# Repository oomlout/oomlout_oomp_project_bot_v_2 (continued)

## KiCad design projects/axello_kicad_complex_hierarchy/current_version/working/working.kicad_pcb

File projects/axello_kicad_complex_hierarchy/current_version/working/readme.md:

# kicad
 
## summary 
* id: axello_kicad_complex_hierarchy
* user: axello
* name: kicad
* board: complex_hierarchy
* repo: https://github.com/axello/kicad
* src_file_repo_kicad_pcb: demos/complex_hierarchy/complex_hierarchy.kicad_pcb
* src_file_repo_kicad_pcb_link: https://github.com/axello/kicad/tree/master/demos/complex_hierarchy/complex_hierarchy.kicad_pcb
* src_file_repo_kicad_sch: demos/complex_hierarchy/ampli_ht.kicad_sch
* src_file_repo_kicad_sch_link: https://github.com/axello/kicad/tree/master/demos/complex_hierarchy/ampli_ht.kicad_sch

* src_file_repo_sch: Arduino_Mega_433Mhz_Shield/Arduino_Mega.sch
* src_file_repo_sch_link: https://github.com/axello/kicad/tree/master/Arduino_Mega_433Mhz_Shield/Arduino_Mega.sch
* full details link: https://github.com/oomlout/oomlout_oomp_project_bot_v_2/tree/main/projects/axello_kicad_complex_hierarchy/current_version/working  

## pcb  

[board (pdf)](working.pdf)  

## working_bom
| Id | Designator | Footprint | Quantity | Designation | Supplier and ref |  | None | 
| --- | --- | --- | --- | --- | --- | --- | --- | 
| 1 | C2 | CP_Axial_L10.0mm_D4.5mm_P15.00mm_Horizontal | 1 | 47uF/20V |  |  | [''] | 
| 2 | C9 | CP_Axial_L11.0mm_D6.0mm_P18.00mm_Horizontal | 1 | 47uF/63V |  |  | [''] | 
| 3 | C10,C11 | CP_Axial_L10.0mm_D4.5mm_P15.00mm_Horizontal | 2 | 10uF |  |  | [''] | 
| 4 | Q1,Q3,Q5,Q7 | TO-92_HandSolder | 4 | MPSA92 |  |  | [''] | 
| 5 | Q6,Q8,Q2,Q4 | TO-92_HandSolder | 4 | MPSA42 |  |  | [''] | 
| 6 | RV1,RV2 | Potentiometer_Bourns_3266W_Vertical | 2 | 4,7K |  |  | [''] | 
| 7 | U2 | TO-92_HandSolder | 1 | 78L05 |  |  | [''] | 
| 8 | R19,R18,R9,R8,R24,R23 | R_Axial_DIN0204_L3.6mm_D1.6mm_P7.62mm_Horizontal | 6 | 1K |  |  | [''] | 
| 9 | R6,R16,R7,R17 | R_Axial_DIN0204_L3.6mm_D1.6mm_P7.62mm_Horizontal | 4 | 22K |  |  | [''] | 
| 10 | R15,R5,R27,R25 | R_Axial_DIN0204_L3.6mm_D1.6mm_P7.62mm_Horizontal | 4 | 47 |  |  | [''] | 
| 11 | R14,R12,R4,R28,R26,R22 | R_Axial_DIN0204_L3.6mm_D1.6mm_P7.62mm_Horizontal | 6 | 220K |  |  | [''] | 
| 12 | R13,R3 | R_Axial_DIN0204_L3.6mm_D1.6mm_P7.62mm_Horizontal | 2 | 470 |  |  | [''] | 
| 13 | R11,R21 | R_Axial_DIN0204_L3.6mm_D1.6mm_P7.62mm_Horizontal | 2 | 4,7K |  |  | [''] | 
| 14 | R10,R20 | R_Axial_DIN0204_L3.6mm_D1.6mm_P7.62mm_Horizontal | 2 | 5,6K |  |  | [''] | 
| 15 | U4,U3 | DIP-8_W7.62mm_LongPads | 2 | LM358N |  |  | [''] | 
| 16 | U1 | DIP-8_W7.62mm_LongPads | 1 | ICL7660 |  |  | [''] | 
| 17 | C8,C5 | C_Disc_D5.0mm_W2.5mm_P5.00mm | 2 | 820pF |  |  | [''] | 
| 18 | C7,C4 | C_Disc_D5.0mm_W2.5mm_P5.00mm | 2 | 4.7nF |  |  | [''] | 
| 19 | C6,C3 | C_Disc_D5.0mm_W2.5mm_P5.00mm | 2 | 15nF |  |  | [''] | 
| 20 | C12,C14 | C_Disc_D5.0mm_W2.5mm_P5.00mm | 2 | 150nF |  |  | [''] | 
| 21 | D1 | D_DO-41_SOD81_P12.70mm_Horizontal | 1 | 1N4007 |  |  | [''] | 
| 22 | D5,D8,D2,D3,D7,D6,D4,D9 | D_DO-35_SOD27_P7.62mm_Horizontal | 8 | 1N4148 |  |  | [''] | 
| 23 | P1,P2,P4,P3,P6,P5 | Altech_AK300_1x02_P5.00mm_45-Degree | 6 | CONN_2 |  |  | [''] | 
| 24 | C1 | CP_Axial_L10.0mm_D4.5mm_P15.00mm_Horizontal | 1 | 47uF |  |  | [''] |

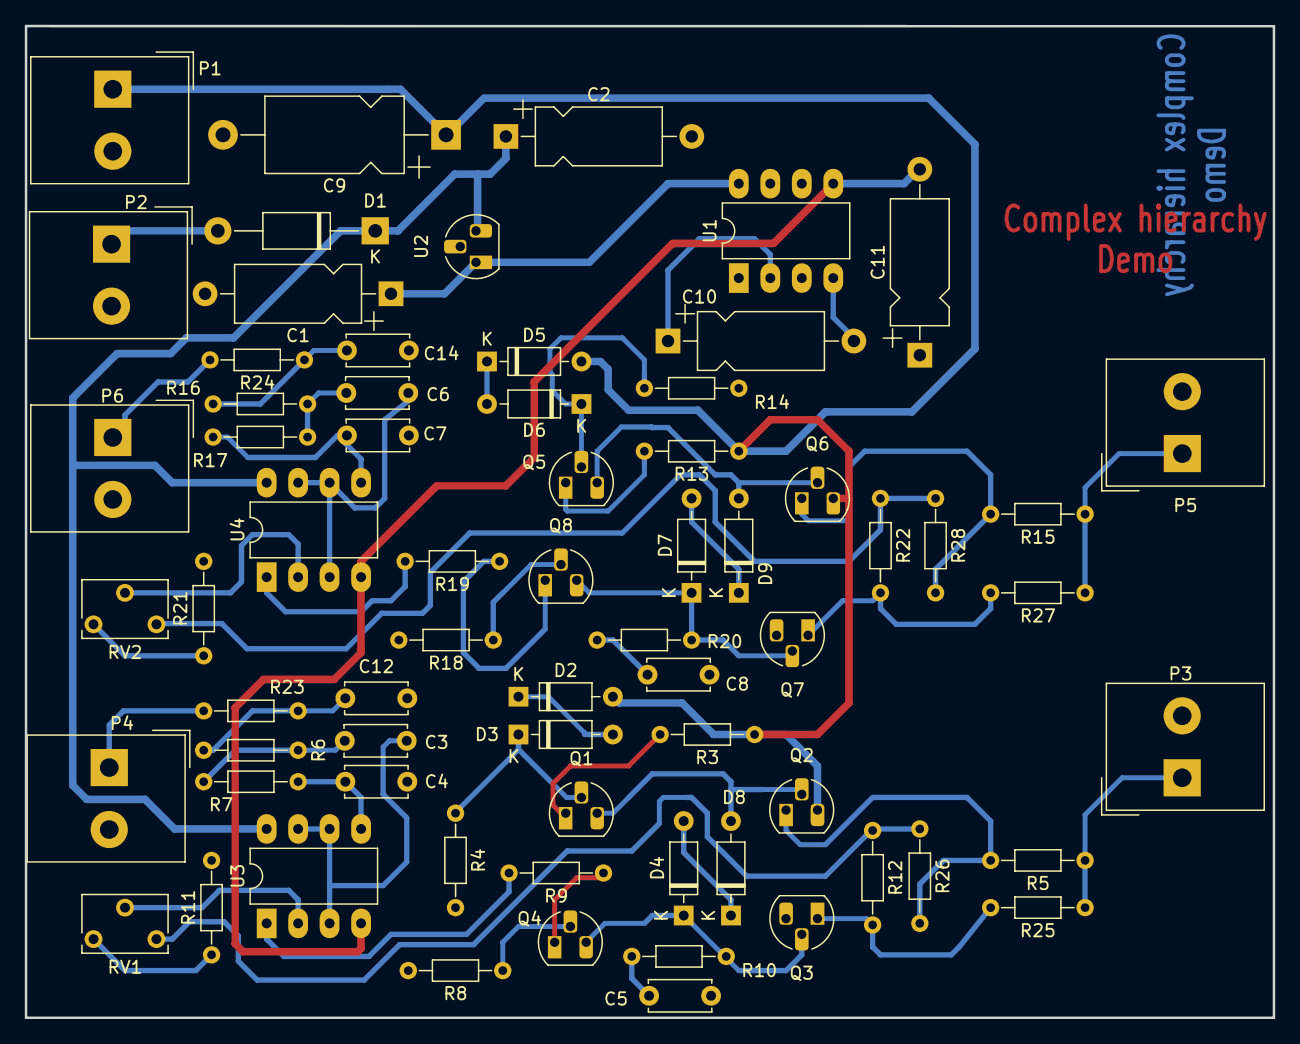
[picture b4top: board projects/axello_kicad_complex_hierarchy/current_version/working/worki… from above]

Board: 2 copper layers, 100.7 x 80.0 mm, 68 parts (0 on the bottom side), 50 nets.

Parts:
C1: 47uF; CP_Axial_L10.0mm_D4.5mm_P15.00mm_Horizontal
C2: 47uF/20V; CP_Axial_L10.0mm_D4.5mm_P15.00mm_Horizontal
C3, C6: 15nF; C_Disc_D5.0mm_W2.5mm_P5.00mm
C4, C7: 4.7nF; C_Disc_D5.0mm_W2.5mm_P5.00mm
C5, C8: 820pF; C_Disc_D5.0mm_W2.5mm_P5.00mm
C9: 47uF/63V; CP_Axial_L11.0mm_D6.0mm_P18.00mm_Horizontal
C10, C11: 10uF; CP_Axial_L10.0mm_D4.5mm_P15.00mm_Horizontal
C12, C14: 150nF; C_Disc_D5.0mm_W2.5mm_P5.00mm
D1: 1N4007; D_DO-41_SOD81_P12.70mm_Horizontal
D2, D3, D4, D5, D6, D7, D8, D9: 1N4148; D_DO-35_SOD27_P7.62mm_Horizontal
P1, P2, P3, P4, P5, P6: CONN_2; Altech_AK300_1x02_P5.00mm_45-Degree
Q1, Q3, Q5, Q7: MPSA92; TO-92_HandSolder
Q2, Q4, Q6, Q8: MPSA42; TO-92_HandSolder
R3, R13: 470; R_Axial_DIN0204_L3.6mm_D1.6mm_P7.62mm_Horizontal
R4, R12, R14, R22, R26, R28: 220K; R_Axial_DIN0204_L3.6mm_D1.6mm_P7.62mm_Horizontal
R5, R15, R25, R27: 47; R_Axial_DIN0204_L3.6mm_D1.6mm_P7.62mm_Horizontal
R6, R7, R16, R17: 22K; R_Axial_DIN0204_L3.6mm_D1.6mm_P7.62mm_Horizontal
R8, R9, R18, R19, R23, R24: 1K; R_Axial_DIN0204_L3.6mm_D1.6mm_P7.62mm_Horizontal
R10, R20: 5,6K; R_Axial_DIN0204_L3.6mm_D1.6mm_P7.62mm_Horizontal
R11, R21: 4,7K; R_Axial_DIN0204_L3.6mm_D1.6mm_P7.62mm_Horizontal
RV1, RV2: 4,7K; Potentiometer_Bourns_3266W_Vertical
U1: ICL7660; DIP-8_W7.62mm_LongPads
U2: 78L05; TO-92_HandSolder
U3, U4: LM358N; DIP-8_W7.62mm_LongPads

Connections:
+12V: C2.1, D1.1 (K), U2.3 (VI), U3.8 (V+), U4.8 (V+)
-VAA: C11.2, U1.5 (VOUT), U3.4 (V-), U4.4 (V-)
/12Vext: D1.2 (A), P2.1
/ampli_ht_horizontal/PIEZO_IN: P6.1, R24.2
/ampli_ht_horizontal/PIEZO_OUT: P5.1, R15.1, R27.1
/ampli_ht_horizontal/S_OUT+: R22.1, R28.1, RV2.3
/ampli_ht_horizontal/Vpil_0_3,3V: C6.1, U4.3 (+), U4.6 (-), U4.7
/ampli_ht_vertical/PIEZO_IN: P4.1, R23.2
/ampli_ht_vertical/PIEZO_OUT: P3.1, R5.1, R25.1
/ampli_ht_vertical/S_OUT+: R12.1, R26.1, RV1.3
/ampli_ht_vertical/Vpil_0_3,3V: C3.1, U3.3 (+), U3.6 (-), U3.7
GND: C1.2, C2.2, C4.2, C5.2, C7.2, C8.2, C9.2, C11.1, C12.2, C14.2, P1.2 (PM), P2.2 (PM), P3.2 (PM), P4.2 (PM), P5.2 (PM), P6.2 (PM), Q3.3 (C), Q7.3 (C), R4.2, R8.2, R11.2, R14.2, R18.2, R21.2, U1.3 (GND), U2.2 (GND)
HT: C9.1, D2.2 (A), D5.2 (A), P1.1, Q2.3 (C), Q6.3 (C), R3.1, R13.1
unnamed: C3.2, R6.1, R7.2
unnamed: C4.1, R7.1, U3.5 (+)
unnamed: C5.1, R10.2
unnamed: C6.2, R16.1, R17.2
unnamed: C7.1, R17.1, U4.5 (+)
unnamed: C8.1, R20.2
unnamed: C10.1, U1.2 (CAP+)
unnamed: C10.2, U1.4 (CAP-)
unnamed: C12.1, R6.2, R23.1
unnamed: C14.1, R16.2, R24.1
unnamed: D2.1 (K), D3.2 (A)
unnamed: D3.1 (K), Q1.2 (B), R4.1
unnamed: D4.1 (K), Q3.2 (B), Q4.3 (C), R10.1
unnamed: D4.2 (A), D8.1 (K)
unnamed: D5.1 (K), D6.2 (A)
unnamed: D6.1 (K), Q5.2 (B), R14.1
unnamed: D7.1 (K), Q7.2 (B), Q8.3 (C), R20.1
unnamed: D7.2 (A), D9.1 (K)
unnamed: D8.2 (A), Q1.3 (C), Q2.2 (B)
unnamed: D9.2 (A), Q5.3 (C), Q6.2 (B)
unnamed: Q1.1 (E), R3.2
unnamed: Q2.1 (E), R5.2, R26.2
unnamed: Q3.1 (E), R12.2, R25.2
unnamed: Q4.1 (E), R9.1
unnamed: Q4.2 (B), R8.1
unnamed: Q5.1 (E), R13.2
unnamed: Q6.1 (E), R15.2, R28.2
unnamed: Q7.1 (E), R22.2, R27.2
unnamed: Q8.1 (E), R19.1
unnamed: Q8.2 (B), R18.1
unnamed: R9.2, U3.1
unnamed: R11.1, RV1.1
unnamed: R19.2, U4.1
unnamed: R21.1, RV2.1
unnamed: RV1.2, U3.2 (-)
unnamed: RV2.2, U4.2 (-)
VCC: C1.1, U1.8 (V+), U2.1 (VO)

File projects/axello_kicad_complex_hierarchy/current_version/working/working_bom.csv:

"Id";"Designator";"Footprint";"Quantity";"Designation";"Supplier and ref";
1;"C2";"CP_Axial_L10.0mm_D4.5mm_P15.00mm_Horizontal";1;"47uF/20V";;;
2;"C9";"CP_Axial_L11.0mm_D6.0mm_P18.00mm_Horizontal";1;"47uF/63V";;;
3;"C10,C11";"CP_Axial_L10.0mm_D4.5mm_P15.00mm_Horizontal";2;"10uF";;;
4;"Q1,Q3,Q5,Q7";"TO-92_HandSolder";4;"MPSA92";;;
5;"Q6,Q8,Q2,Q4";"TO-92_HandSolder";4;"MPSA42";;;
6;"RV1,RV2";"Potentiometer_Bourns_3266W_Vertical";2;"4,7K";;;
7;"U2";"TO-92_HandSolder";1;"78L05";;;
8;"R19,R18,R9,R8,R24,R23";"R_Axial_DIN0204_L3.6mm_D1.6mm_P7.62mm_Horizontal";6;"1K";;;
9;"R6,R16,R7,R17";"R_Axial_DIN0204_L3.6mm_D1.6mm_P7.62mm_Horizontal";4;"22K";;;
10;"R15,R5,R27,R25";"R_Axial_DIN0204_L3.6mm_D1.6mm_P7.62mm_Horizontal";4;"47";;;
11;"R14,R12,R4,R28,R26,R22";"R_Axial_DIN0204_L3.6mm_D1.6mm_P7.62mm_Horizontal";6;"220K";;;
12;"R13,R3";"R_Axial_DIN0204_L3.6mm_D1.6mm_P7.62mm_Horizontal";2;"470";;;
13;"R11,R21";"R_Axial_DIN0204_L3.6mm_D1.6mm_P7.62mm_Horizontal";2;"4,7K";;;
14;"R10,R20";"R_Axial_DIN0204_L3.6mm_D1.6mm_P7.62mm_Horizontal";2;"5,6K";;;
15;"U4,U3";"DIP-8_W7.62mm_LongPads";2;"LM358N";;;
16;"U1";"DIP-8_W7.62mm_LongPads";1;"ICL7660";;;
17;"C8,C5";"C_Disc_D5.0mm_W2.5mm_P5.00mm";2;"820pF";;;
18;"C7,C4";"C_Disc_D5.0mm_W2.5mm_P5.00mm";2;"4.7nF";;;
19;"C6,C3";"C_Disc_D5.0mm_W2.5mm_P5.00mm";2;"15nF";;;
20;"C12,C14";"C_Disc_D5.0mm_W2.5mm_P5.00mm";2;"150nF";;;
21;"D1";"D_DO-41_SOD81_P12.70mm_Horizontal";1;"1N4007";;;
22;"D5,D8,D2,D3,D7,D6,D4,D9";"D_DO-35_SOD27_P7.62mm_Horizontal";8;"1N4148";;;
23;"P1,P2,P4,P3,P6,P5";"Altech_AK300_1x02_P5.00mm_45-Degree";6;"CONN_2";;;
24;"C1";"CP_Axial_L10.0mm_D4.5mm_P15.00mm_Horizontal";1;"47uF";;;

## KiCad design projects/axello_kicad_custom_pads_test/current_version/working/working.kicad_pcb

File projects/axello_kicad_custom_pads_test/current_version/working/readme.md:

# kicad
 
## summary 
* id: axello_kicad_custom_pads_test
* user: axello
* name: kicad
* board: custom_pads_test
* repo: https://github.com/axello/kicad
* src_file_repo_kicad_pcb: demos/custom_pads_test/custom_pads_test.kicad_pcb
* src_file_repo_kicad_pcb_link: https://github.com/axello/kicad/tree/master/demos/custom_pads_test/custom_pads_test.kicad_pcb
* src_file_repo_kicad_sch: demos/custom_pads_test/custom_pads_test.kicad_sch
* src_file_repo_kicad_sch_link: https://github.com/axello/kicad/tree/master/demos/custom_pads_test/custom_pads_test.kicad_sch

* src_file_repo_sch: Arduino_Mega_433Mhz_Shield/Arduino_Mega.sch
* src_file_repo_sch_link: https://github.com/axello/kicad/tree/master/Arduino_Mega_433Mhz_Shield/Arduino_Mega.sch
* full details link: https://github.com/oomlout/oomlout_oomp_project_bot_v_2/tree/main/projects/axello_kicad_custom_pads_test/current_version/working  

## schematic  
  
[schematic (pdf)](working_schematic.pdf) 

## pcb  

[board (pdf)](working.pdf)  

## working_bom
| Id | Designator | Footprint | Quantity | Designation | Supplier and ref |  | None | 
| --- | --- | --- | --- | --- | --- | --- | --- | 
| 1 | R2 | DO-214AB | 1 | R |  |  | [''] | 
| 2 | AE2,AE1 | 1pin | 2 | Antenna |  |  | [''] | 
| 3 | U*** | DIP-14__300_ELL | 1 | DIP-14_300_ELL |  |  | [''] | 
| 4 | SW1 | C2 | 1 | R |  |  | [''] | 

## bom_schematic
| Ref | Qnty | Value | Cmp name | Footprint | Description | Vendor | DNP | 
| --- | --- | --- | --- | --- | --- | --- | --- | 
| AE1, AE2 | 2 | Antenna | Antenna |  |  |  |  | 
| R2 | 1 | R | R |  |  |  |  | 
| SW1 | 1 | R | Jumper-device |  |  |  |  |

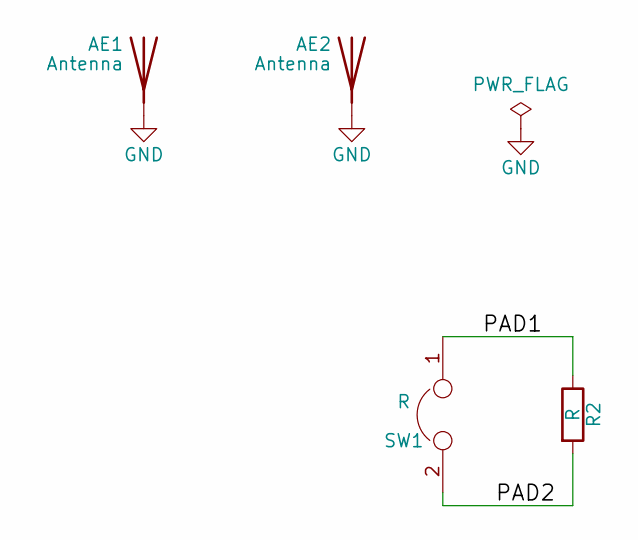
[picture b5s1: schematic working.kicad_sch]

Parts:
AE1, AE2: Antenna
R2: R
SW1: R

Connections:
/PAD1: R2.1, SW1.1
/PAD2: R2.2, SW1.2
GND: AE1.1 (A), AE2.1 (A)

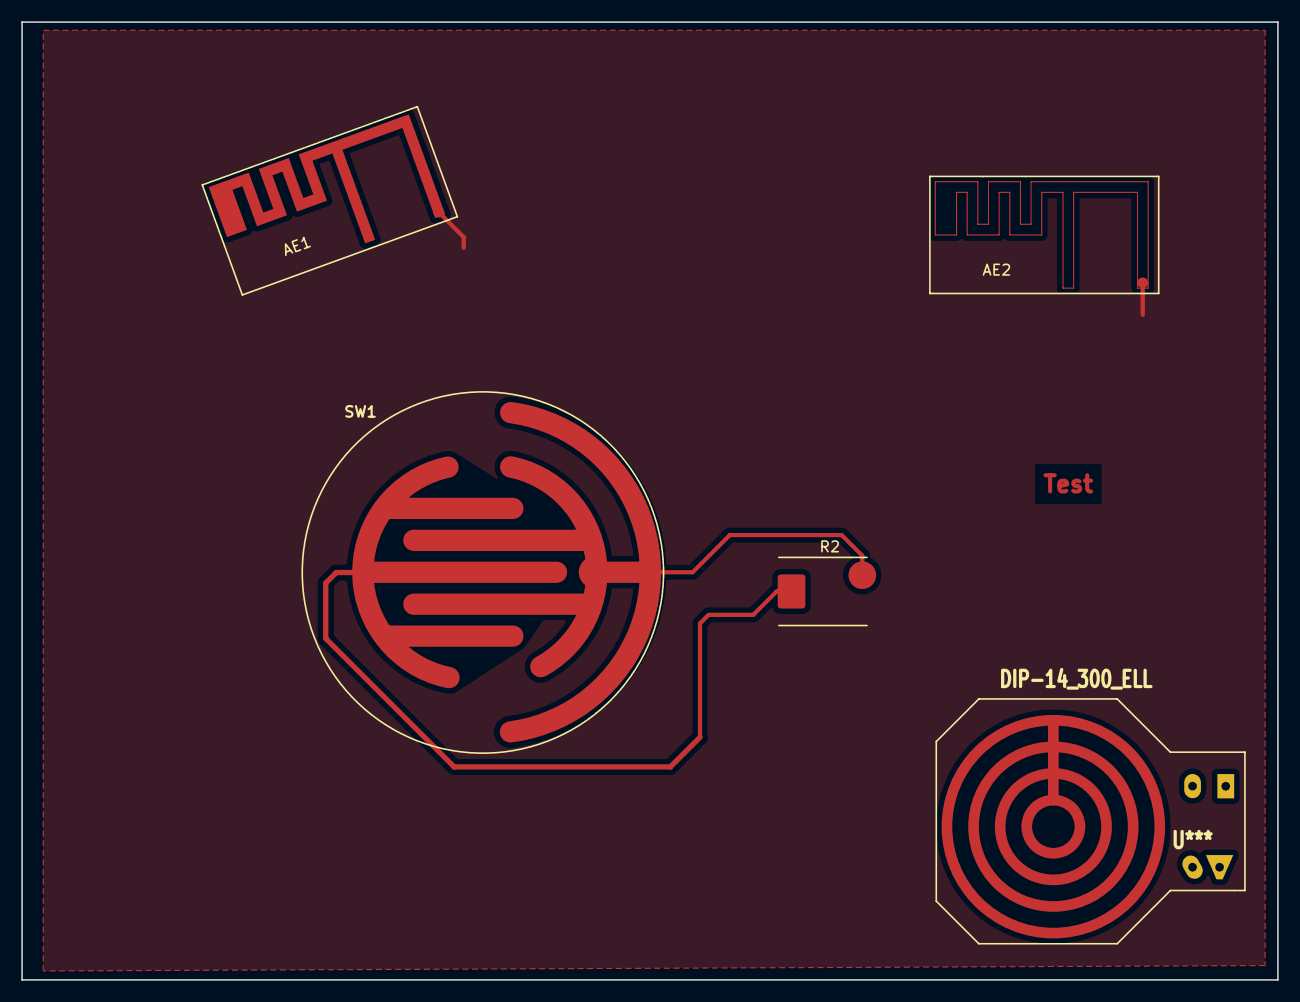
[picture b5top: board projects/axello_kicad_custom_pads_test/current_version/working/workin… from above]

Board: 2 copper layers, 118.0 x 90.0 mm, 5 parts (0 on the bottom side), 3 nets.

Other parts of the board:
U***: DIP-14_300_ELL; DIP-14__300_ELL

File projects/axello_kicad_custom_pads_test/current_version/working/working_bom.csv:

"Id";"Designator";"Footprint";"Quantity";"Designation";"Supplier and ref";
1;"R2";"DO-214AB";1;"R";;;
2;"AE2,AE1";"1pin";2;"Antenna";;;
3;"U***";"DIP-14__300_ELL";1;"DIP-14_300_ELL";;;
4;"SW1";"C2";1;"R";;;

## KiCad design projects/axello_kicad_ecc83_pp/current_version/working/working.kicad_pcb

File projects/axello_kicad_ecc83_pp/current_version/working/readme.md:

# kicad
 
## summary 
* id: axello_kicad_ecc83_pp
* user: axello
* name: kicad
* board: ecc83_pp
* repo: https://github.com/axello/kicad
* src_file_repo_kicad_pcb: demos/ecc83/ecc83-pp.kicad_pcb
* src_file_repo_kicad_pcb_link: https://github.com/axello/kicad/tree/master/demos/ecc83/ecc83-pp.kicad_pcb
* src_file_repo_kicad_sch: demos/ecc83/ecc83-pp.kicad_sch
* src_file_repo_kicad_sch_link: https://github.com/axello/kicad/tree/master/demos/ecc83/ecc83-pp.kicad_sch

* src_file_repo_sch: Arduino_Mega_433Mhz_Shield/Arduino_Mega.sch
* src_file_repo_sch_link: https://github.com/axello/kicad/tree/master/Arduino_Mega_433Mhz_Shield/Arduino_Mega.sch
* full details link: https://github.com/oomlout/oomlout_oomp_project_bot_v_2/tree/main/projects/axello_kicad_ecc83_pp/current_version/working  

## schematic  
  
[schematic (pdf)](working_schematic.pdf) 

## pcb  

[board (pdf)](working.pdf)  

## working_bom
| Id | Designator | Footprint | Quantity | Designation | Supplier and ref |  | None | 
| --- | --- | --- | --- | --- | --- | --- | --- | 
| 1 | C1 | CP_Radial_D10.0mm_P5.00mm | 1 | 10uF |  |  | [''] | 
| 2 | C2 | C_Disc_D4.7mm_W2.5mm_P5.00mm | 1 | 680nF |  |  | [''] | 
| 3 | R1,R2 | R_Axial_DIN0207_L6.3mm_D2.5mm_P7.62mm_Horizontal | 2 | 1.5K |  |  | [''] | 
| 4 | R4 | R_Axial_DIN0207_L6.3mm_D2.5mm_P7.62mm_Horizontal | 1 | 47K |  |  | [''] | 
| 5 | P2 | Altech_AK300_1x02_P5.00mm_45-Degree | 1 | OUT |  |  | [''] | 
| 6 | P3 | Altech_AK300_1x02_P5.00mm_45-Degree | 1 | POWER |  |  | [''] | 
| 7 | P4 | Altech_AK300_1x02_P5.00mm_45-Degree | 1 | CONN_2 |  |  | [''] | 
| 8 | R3 | R_Axial_DIN0207_L6.3mm_D2.5mm_P7.62mm_Horizontal | 1 | 100K |  |  | [''] | 
| 9 | U1 | Valve_ECC-83-1 | 1 | ECC83 |  |  | [''] | 
| 10 | P1 | Altech_AK300_1x02_P5.00mm_45-Degree | 1 | IN |  |  | [''] | 

## bom_schematic
| Ref | Qnty | Value | Cmp name | Footprint | Description | Vendor | DNP | 
| --- | --- | --- | --- | --- | --- | --- | --- | 
| C1 | 1 | 10uF | CP | Capacitor_THT:CP_Radial_D10.0mm_P5.00mm | Polarised capacitor |  |  | 
| C2 | 1 | 680nF | C | Capacitor_THT:C_Disc_D4.7mm_W2.5mm_P5.00mm |  |  |  | 
| P1 | 1 | IN | CONN_2 | TerminalBlock_Altech:Altech_AK300_1x02_P5.00mm_45-Degree |  |  |  | 
| P2 | 1 | OUT | CONN_2 | TerminalBlock_Altech:Altech_AK300_1x02_P5.00mm_45-Degree |  |  |  | 
| P3 | 1 | POWER | CONN_2 | TerminalBlock_Altech:Altech_AK300_1x02_P5.00mm_45-Degree |  |  |  | 
| P4 | 1 | CONN_2 | CONN_2 | TerminalBlock_Altech:Altech_AK300_1x02_P5.00mm_45-Degree |  |  |  | 
| P5, P6, P7, P8 | 4 | MOUNTING_HOLE | CONN_1 | MountingHole:MountingHole_3.2mm_M3_DIN965_Pad |  |  |  | 
| R1, R2 | 2 | 1.5K | R | Resistor_THT:R_Axial_DIN0207_L6.3mm_D2.5mm_P7.62mm_Horizontal |  |  |  | 
| R3 | 1 | 100K | R | Resistor_THT:R_Axial_DIN0207_L6.3mm_D2.5mm_P7.62mm_Horizontal |  |  |  | 
| R4 | 1 | 47K | R | Resistor_THT:R_Axial_DIN0207_L6.3mm_D2.5mm_P7.62mm_Horizontal |  |  |  | 
| U1 | 1 | ECC83 | ECC83 | Valve:Valve_ECC-83-1 |  |  |  |

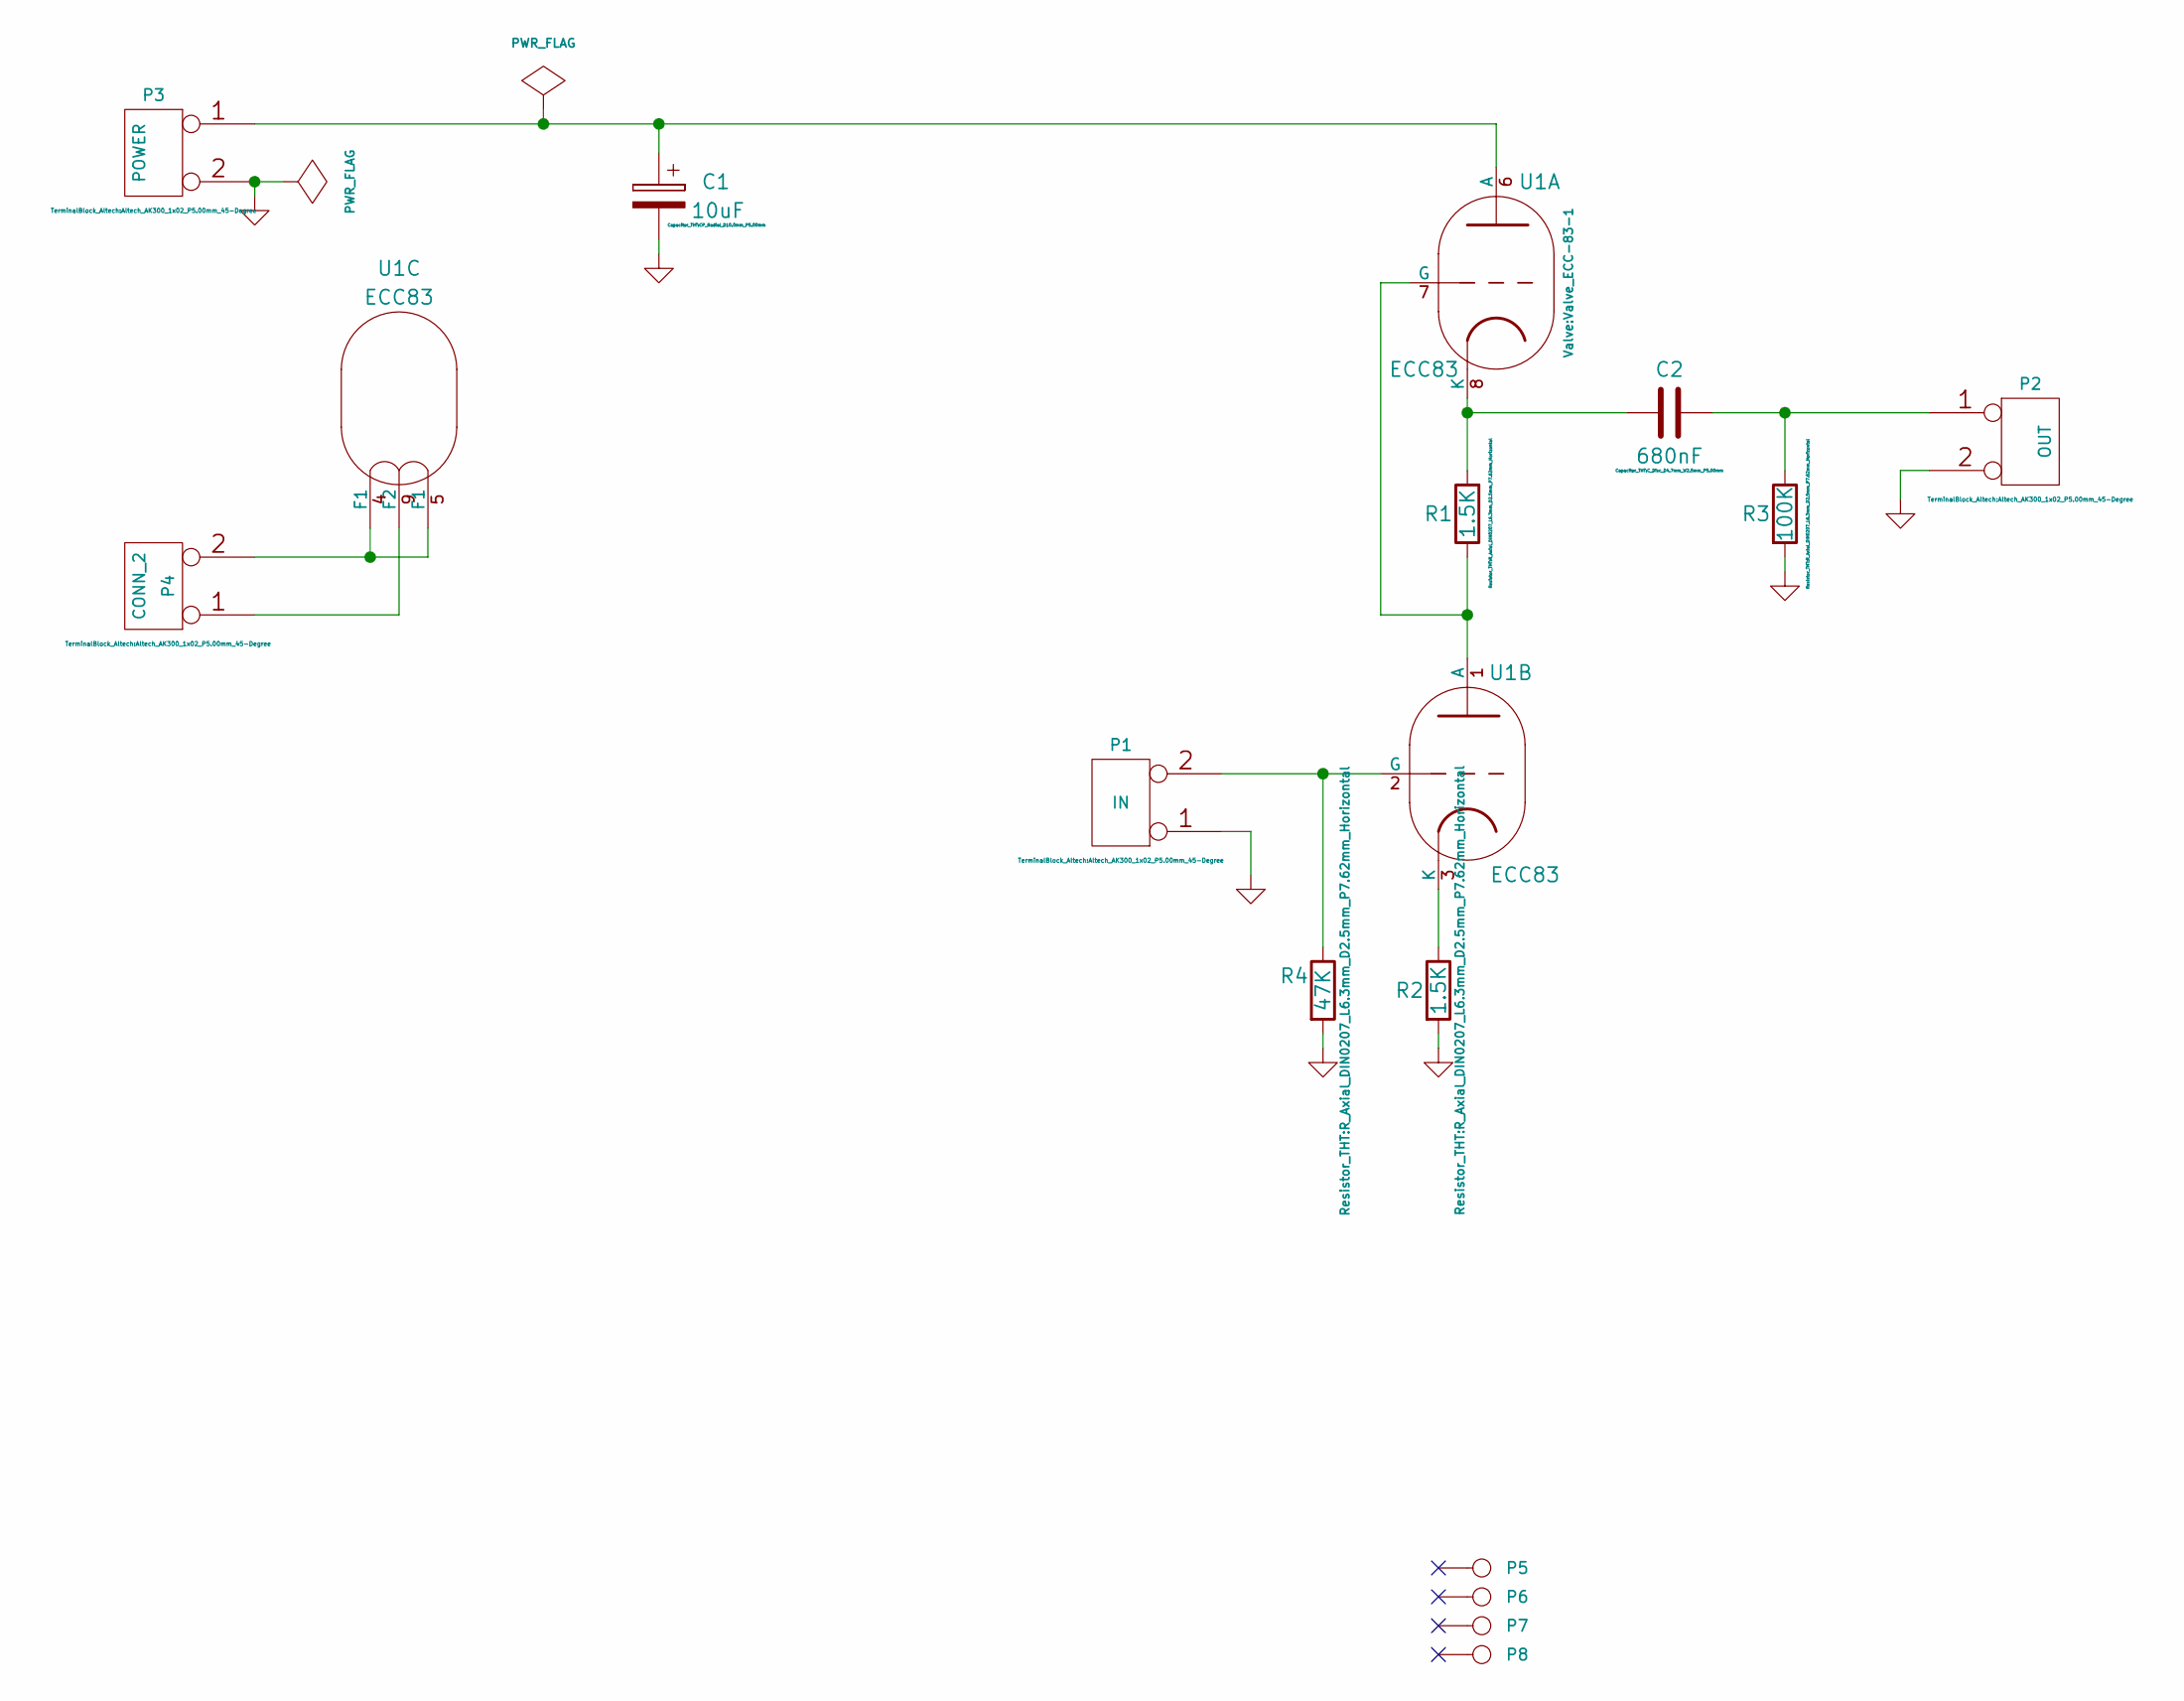
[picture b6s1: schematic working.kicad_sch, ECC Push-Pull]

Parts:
C1: 10uF; CP_Radial_D10.0mm_P5.00mm
C2: 680nF; C_Disc_D4.7mm_W2.5mm_P5.00mm
P1: IN; Altech_AK300_1x02_P5.00mm_45-Degree
P2: OUT; Altech_AK300_1x02_P5.00mm_45-Degree
P3: POWER; Altech_AK300_1x02_P5.00mm_45-Degree
P4: CONN_2; Altech_AK300_1x02_P5.00mm_45-Degree
P5, P6, P7, P8: MOUNTING_HOLE; MountingHole_3.2mm_M3_DIN965_Pad
R1, R2: 1.5K; R_Axial_DIN0207_L6.3mm_D2.5mm_P7.62mm_Horizontal
R3: 100K; R_Axial_DIN0207_L6.3mm_D2.5mm_P7.62mm_Horizontal
R4: 47K; R_Axial_DIN0207_L6.3mm_D2.5mm_P7.62mm_Horizontal
U1: ECC83; Valve_ECC-83-1

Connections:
GND: C1.2, P1.1, P2.2 (PM), P3.2 (PM), R2.2, R3.2, R4.2
unnamed: C1.1, P3.1, U1.6 (A)
unnamed: C2.1, P2.1, R3.1
unnamed: C2.2, R1.2, U1.8 (K)
unnamed: P1.2 (PM), R4.1, U1.2 (G)
unnamed: P4.1, U1.9 (F2)
unnamed: P4.2 (PM), U1.4 (F1), U1.5 (F1)
unnamed: R1.1, U1.1 (A), U1.7 (G)
unnamed: R2.1, U1.3 (K)

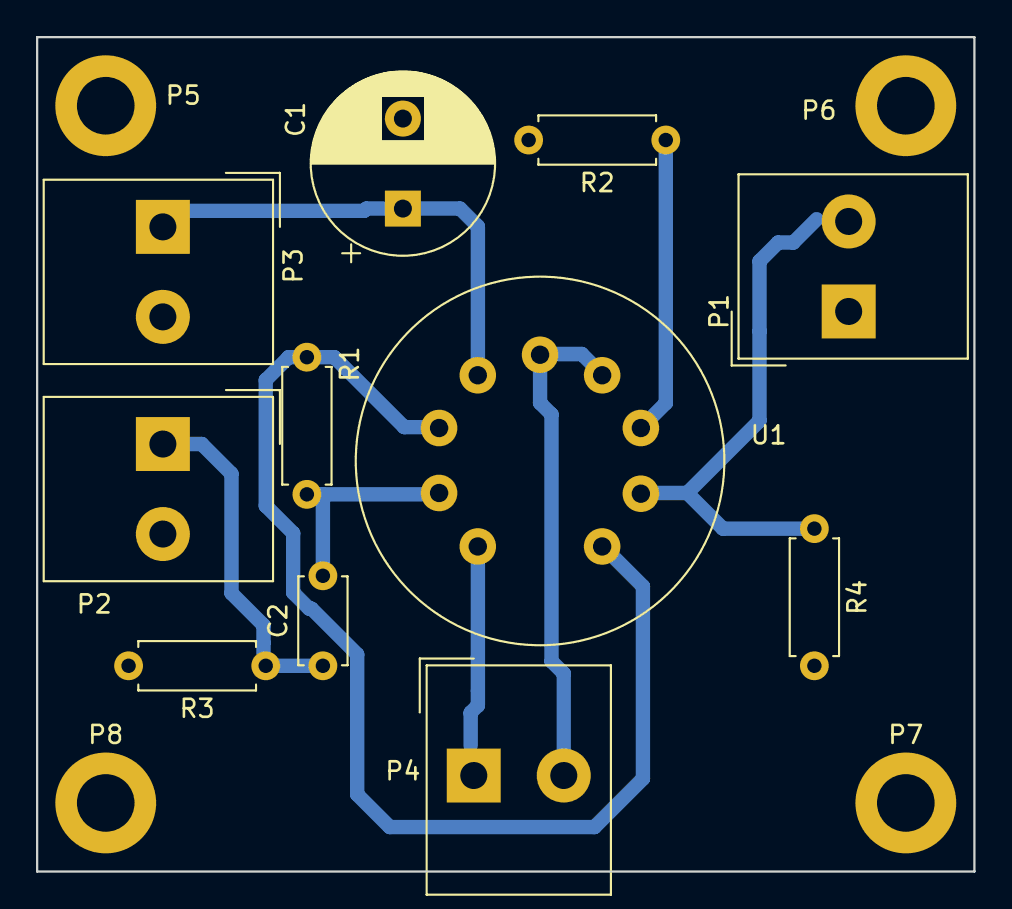
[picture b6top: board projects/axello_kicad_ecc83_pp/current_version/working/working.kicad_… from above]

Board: 2 copper layers, 52.1 x 46.4 mm, 15 parts (0 on the bottom side), 9 nets.

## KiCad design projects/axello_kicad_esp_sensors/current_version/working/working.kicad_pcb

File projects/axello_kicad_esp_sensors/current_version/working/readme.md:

# kicad
 
## summary 
* id: axello_kicad_esp_sensors
* user: axello
* name: kicad
* board: esp_sensors
* repo: https://github.com/axello/kicad
* src_file_repo_kicad_pcb: ESP-Sensors/ESP-Sensors.kicad_pcb
* src_file_repo_kicad_pcb_link: https://github.com/axello/kicad/tree/master/ESP-Sensors/ESP-Sensors.kicad_pcb
* src_file_repo_kicad_sch: ESP-Sensors/ESP-Sensors.kicad_sch
* src_file_repo_kicad_sch_link: https://github.com/axello/kicad/tree/master/ESP-Sensors/ESP-Sensors.kicad_sch

* src_file_repo_sch: ESP-Sensors/ESP-Sensors.sch
* src_file_repo_sch_link: https://github.com/axello/kicad/tree/master/ESP-Sensors/ESP-Sensors.sch
* full details link: https://github.com/oomlout/oomlout_oomp_project_bot_v_2/tree/main/projects/axello_kicad_esp_sensors/current_version/working  

## schematic  
  
[schematic (pdf)](working_schematic.pdf) 

[schematic 1 (pdf)](working_1_schematic.pdf) 

## pcb  

[board (pdf)](working.pdf)  

## working_bom
| Id | Designator | Footprint | Quantity | Designation | Supplier and ref |  | None | 
| --- | --- | --- | --- | --- | --- | --- | --- | 
| 1 | C1,C2 | C_0805_HandSoldering | 2 | 100nF |  |  | [''] | 
| 2 | C3 | c_elec_6.3x7.7 | 1 | 100ÂµF |  |  | [''] | 
| 3 | J2 | Pin_Header_Straight_1x12 | 1 | GPIO |  |  | [''] | 
| 4 | J4 | Pin_Header_Straight_1x04 | 1 | +3.3V GND +5V |  |  | [''] | 
| 5 | R1,R2,R3,R4 | R_0805_HandSoldering | 4 | 10K |  |  | [''] | 
| 6 | SW1 | SW_PUSH_6mm | 1 | RESET |  |  | [''] | 
| 7 | SW2 | SW_PUSH_6mm | 1 | PROG |  |  | [''] | 
| 8 | U1 | ESP-12E | 1 | ESP-12E |  |  | [''] | 
| 9 | REF**,REF**,REF**,REF** | MountingHole_3.2mm_M3 | 4 | MountingHole_3.2mm_M3 |  |  | [''] | 
| 10 |  | proto_grid_6x10 | 1 | proto_grid_6x10 |  |  | [''] | 
| 11 | REF**,REF** | Pin_Header_Straight_1x06 | 2 | GPIO |  |  | [''] | 
| 12 | J5 | Pin_Header_Straight_1x02 | 1 | DEEP_SLEEP |  |  | [''] | 
| 13 | 10K1 | Potentiometer_Trimmer_Vishay_T73YP_Horizontal | 1 | POT |  |  | [''] | 
| 14 | J3 | SPI_Header | 1 | SPI |  |  | [''] | 
| 15 | U2 | SOT89-3_Housing_Handsoldering | 1 | HT7333 |  |  | [''] | 
| 16 | J1 | Pin_Header_Straight_1x05b | 1 | PROG_CONN |  |  | [''] | 
| 17 | G*** | LOGO2 | 1 | LOGO |  |  | [''] | 

## bom_schematic
| Ref | Qnty | Value | Cmp name | Footprint | Description | Vendor | DNP | 
| --- | --- | --- | --- | --- | --- | --- | --- | 
| 10K1 | 1 | POT | POT | Potentiometers:Potentiometer_Trimmer_Vishay_T73YP_Horizontal |  |  |  | 
| C1, C2 | 2 | 100nF | C | Capacitors_SMD:C_0805_HandSoldering |  |  |  | 
| C3 | 1 | 100ÂµF | C | Capacitors_SMD:c_elec_6.3x7.7 |  |  |  | 
| J1 | 1 | PROG_CONN | PROG_CONN | ESP-RS232:Pin_Header_Straight_1x05b |  |  |  | 
| J2 | 1 | GPIO | CONN_01X12 | Pin_Headers:Pin_Header_Straight_1x12 |  |  |  | 
| J3 | 1 | SPI | CONN_01X05 | ESP-RS232:SPI_Header |  |  |  | 
| J4 | 1 | +3.3V GND +5V | CONN_01X04 | Pin_Headers:Pin_Header_Straight_1x04 |  |  |  | 
| J5 | 1 | DEEP_SLEEP | CONN_01X02 | Pin_Headers:Pin_Header_Straight_1x02 |  |  |  | 
| R1, R2, R3, R4 | 4 | 10K | R | Resistors_SMD:R_0805_HandSoldering |  |  |  | 
| SW1 | 1 | RESET | SW_Push | Buttons_Switches_THT:SW_PUSH_6mm |  |  |  | 
| SW2 | 1 | PROG | SW_Push | Buttons_Switches_THT:SW_PUSH_6mm |  |  |  | 
| U1 | 1 | ESP-12E | ESP-12E | ESP8266:ESP-12E |  |  |  | 
| U2 | 1 | HT7333 | HT7333 | TO_SOT_Packages_SMD:SOT89-3_Housing_Handsoldering |  |  |  | 

## mounting_holes
| x | y | package | value | ref | size | 
| --- | --- | --- | --- | --- | --- | 
| 0.0 | 46.35 | MountingHole_3.2mm_M3 | MountingHole_3.2mm_M3 | REF** | m3 | 
| 0.0 | 0.0 | MountingHole_3.2mm_M3 | MountingHole_3.2mm_M3 | REF** | m3 | 
| 50.8 | 46.35 | MountingHole_3.2mm_M3 | MountingHole_3.2mm_M3 | REF** | m3 | 
| 50.8 | 0.0 | MountingHole_3.2mm_M3 | MountingHole_3.2mm_M3 | REF** | m3 |

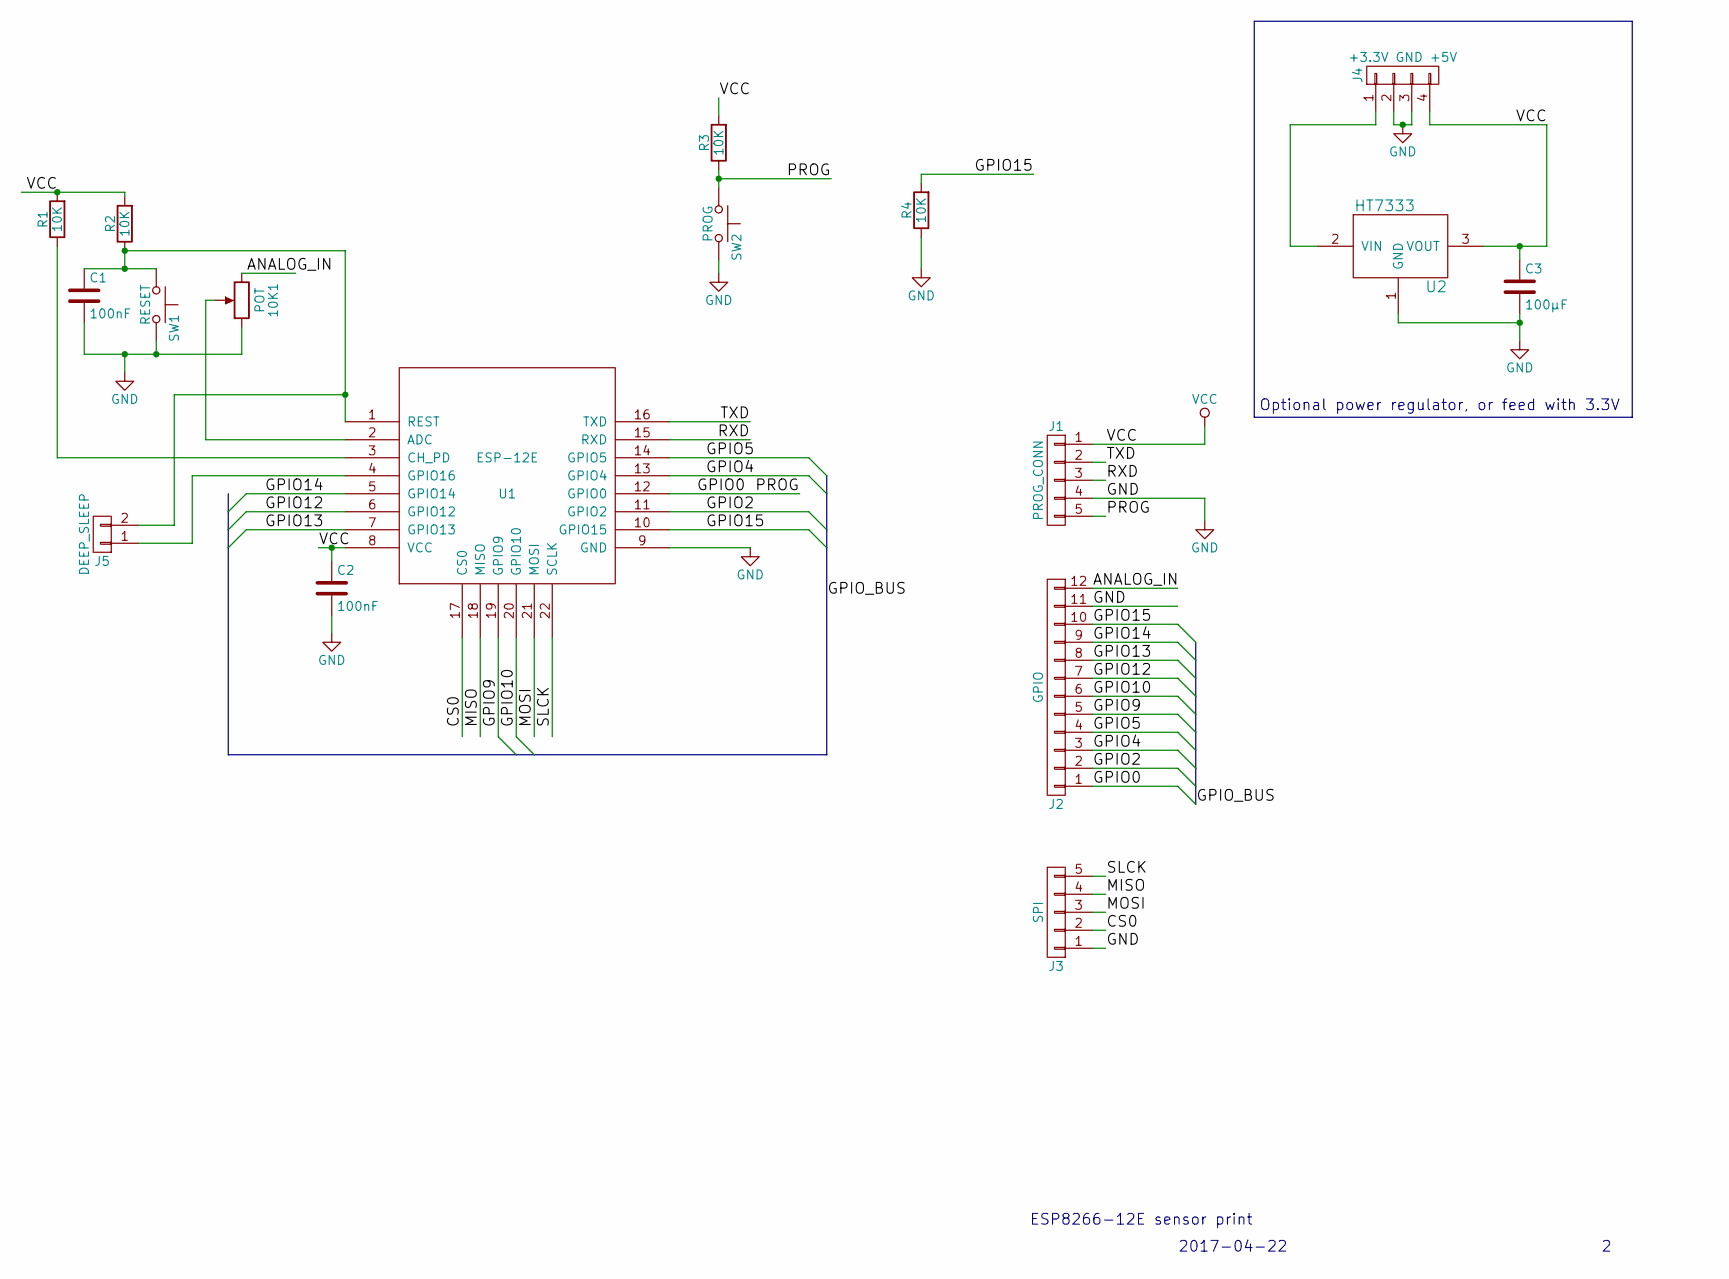
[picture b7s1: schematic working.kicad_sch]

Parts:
10K1: POT; Potentiometer_Trimmer_Vishay_T73YP_Horizontal
C1, C2: 100nF; C_0805_HandSoldering
C3: 100µF; c_elec_6.3x7.7
J1: PROG_CONN; Pin_Header_Straight_1x05b
J2: GPIO; Pin_Header_Straight_1x12
J3: SPI; SPI_Header
J4: +3.3V GND +5V; Pin_Header_Straight_1x04
J5: DEEP_SLEEP; Pin_Header_Straight_1x02
R1, R2, R3, R4: 10K; R_0805_HandSoldering
SW1: RESET; SW_PUSH_6mm
SW2: PROG; SW_PUSH_6mm
U1: ESP-12E
U2: HT7333; SOT89-3_Housing_Handsoldering

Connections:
/ANALOG_IN: 10K1.3, J2.12
/CS0: J3.2, U1.17 (CS0)
/GPIO0: J1.5, J2.1, R3.1, SW2.1, U1.12 (GPIO0)
/GPIO2: J2.2, U1.11 (GPIO2)
/GPIO4: J2.3, U1.13 (GPIO4)
/GPIO5: J2.4, U1.14 (GPIO5)
/GPIO9: J2.5, U1.19 (GPIO9)
/GPIO10: J2.6, U1.20 (GPIO10)
/GPIO12: J2.7, U1.6 (GPIO12)
/GPIO13: J2.8, U1.7 (GPIO13)
/GPIO14: J2.9, U1.5 (GPIO14)
/GPIO15: J2.10, R4.2, U1.10 (GPIO15)
/MISO: J3.4, U1.18 (MISO)
/MOSI: J3.3, U1.21 (MOSI)
/RXD: J1.3, U1.15 (RXD)
/SLCK: J3.5, U1.22 (SCLK)
/TXD: J1.2, U1.16 (TXD)
GND: 10K1.1, C1.2, C2.2, C3.2, J1.4, J2.11, J3.1, J4.2, J4.3, R4.1, SW1.2, SW2.2, U1.9 (GND), U2.1 (GND)
unnamed: 10K1.2, U1.2 (ADC)
unnamed: C1.1, J5.2, R2.1, SW1.1, U1.1 (REST)
unnamed: J4.1, U2.2 (VIN)
unnamed: J5.1, U1.4 (GPIO16)
unnamed: R1.1, U1.3 (CH_PD)
VCC: C2.1, C3.1, J1.1, J4.4, R1.2, R2.2, R3.2, U1.8 (VCC), U2.3 (VOUT)

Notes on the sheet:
Optional power regulator, or feed with 3.3V
2017-04-22
ESP8266-12E sensor print

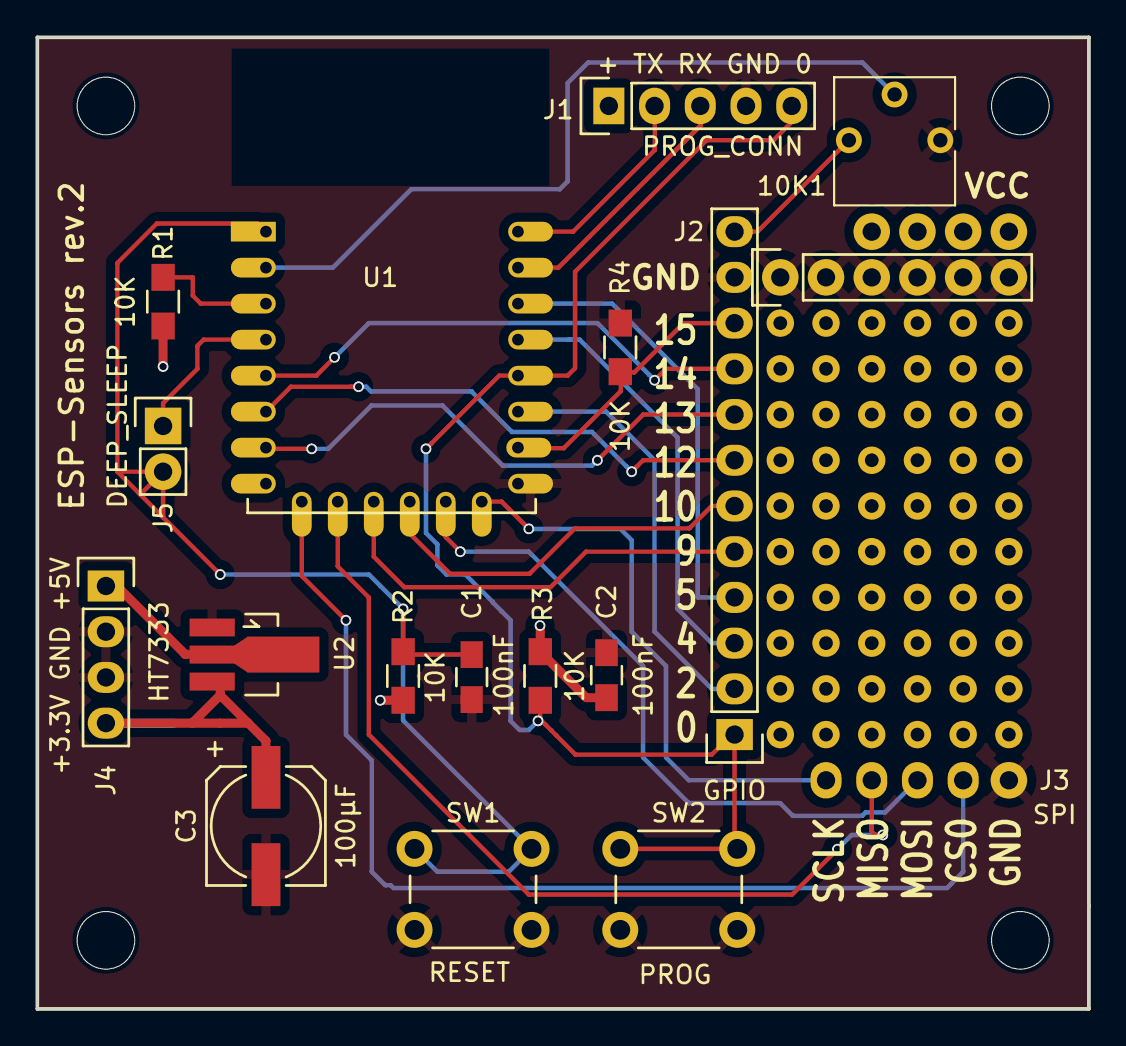
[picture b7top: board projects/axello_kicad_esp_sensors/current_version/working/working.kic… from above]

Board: 2 copper layers, 58.4 x 54.0 mm, 17 parts (0 on the bottom side), 24 nets.
